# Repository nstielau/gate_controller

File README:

# Gate controller

For alexa enabled gate

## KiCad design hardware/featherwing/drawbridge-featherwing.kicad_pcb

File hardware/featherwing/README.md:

# Drawbridge FeatherWing fabrication package

This is a revision-stamped prototype board for a Feather-compatible host,
including the Unexpected Maker FeatherS3[D] and Adafruit ESP32-S3 Reverse TFT
Feather. It provides the existing, proven 2N3904 transistor output unchanged:
J3 pin 1 is the switched output and J3 pin 2 is the shared ground. The Feather
module is not part of the assembly BOM.

Schematic and PCB signal names use portable Feather header labels:
`WIFI_D5`, `MQTT_D6`, `HOLD_D9`, and `CTRL_D11`. GPIO numbers differ between
Feather models and therefore are not part of these net names.

## PCBWay upload

The generated PCB is `drawbridge-featherwing.kicad_pcb` and the schematic is
`drawbridge-featherwing.kicad_sch`. Generate the fabrication package from the
repository root with:

```sh
make featherwing-fab
```

Every run regenerates the design from `generate.py`, runs ERC/DRC, and replaces
the **entire** `artifacts/featherwing/` directory with a complete release. Do not
keep manual edits or source files in that output directory. Old extracted ZIPs,
previews and reports disappear automatically. Other artifact folders are separate.
If a build fails, the last complete release remains available; its timestamp in
`manifest.json` identifies when it was built. Never upload after a failed build
assuming that the files reflect your latest source changes.

Each build requires a **clean Git checkout**, including staged, unstaged, and
untracked files anywhere in the repository. Commit changes before running the
build. Ignored files such as credentials and `artifacts/` do not block it.
There is no dirty-build override or generation counter.

The revision is exactly the first three characters of Git `HEAD`, for example
`abc`, with no suffix. It appears below the castle and in `manifest.json`.
Every ZIP contains `REV_abc.txt` with both `abc` and the **full commit hash**;
use the full hash to identify a commit unambiguously. Rebuilding the same commit
keeps the same revision. The build checks checkout cleanliness and HEAD again
before replacing the output.

Generation runs on a temporary snapshot of committed sources and leaves the
checkout unchanged. The freshly stamped native KiCad project is exported to
`artifacts/featherwing/design/` and included in the combined ZIP. Open that
project to inspect the current release; tracked native KiCad files are reference
snapshots and may carry an older revision. Incorporate edits into the generator,
commit them, then rebuild.

Prerequisites: KiCad 10 in `/Applications/KiCad`, `make setup`, and the repository's
Node/Playwright installation (`make web-setup`, then `npx playwright install chromium`
if Chromium is missing). Incorporate manual KiCad edits into `generate.py` before
rebuilding because the generator is the design source of record.

PCBWay uploads from `artifacts/featherwing/`:

| Upload field | File |
| --- | --- |
| Gerbers | `drawbridge-featherwing-gerbers.zip` |
| Parts list / BOM | `assembly-bom.xlsx` (PCBWay upload) |
| Centroid | `assembly-position.csv` |
| Assembly other files | `drawbridge-featherwing-assembly-other.zip` |
| Complete package for review | `drawbridge-featherwing-pcbway.zip` |

For Seeed Studio Fusion, upload `seeed-assembly-bom.csv`. It uses Seeed's
four-column `Designator`, `Manufacturer Part Number or Seeed SKU`, `Qty`, and
`Link` format and consolidates identical MPNs. All parts except J3 are selected from Seeed's Shenzhen Open Parts Library
(OPL); their links search the live OPL listing. J3 is Phoenix Contact 1725656
and uses its manufacturer link for external sourcing by Seeed (not verified
OPL stock). The BOM includes the two underside Feather headers, five resistors,
Q1, three LEDs, and J3. The Feather host is excluded. Check live availability when requesting a quote because OPL stock
changes independently of this repository.

The selected XKB headers have 2.54 mm pitch, 2.5 mm insulators, 3.0 mm solder
tails, and 6.0 mm mating pins. Seeed must install their bodies on the bottom of
the wing, with the 6.0 mm pins pointing down into the Feather's sockets. The
LEDs are a matching Everlight 3 mm family; observe the KiCad cathode/pad-1
orientation during assembly.

All three ZIPs are generated together and every member is byte-checked against
the corresponding loose file. Gerbers and drills are also available in `gerbers/`
and `drills/`. Each run refreshes `board.png`, `schematic.pdf`, `schematic.svg`,
`schematic.png`, `silkscreen.svg`, logo SVG/PNG, BOM, positions, `netlist.xml`,
`erc.rpt`, `drc.rpt`, and assembly notes. `manifest.json` records the build time
and SHA-256 for every loose file and ZIP (excluding the manifest itself).
The BOM is emitted as both `assembly-bom.xlsx` for PCBWay and `assembly-bom.csv`
for review. Both include an explicit `Tolerance` column: all five resistors
(R1–R5) have a tolerance of **5%**. R1/R3/R4/R5 are 1 kΩ Yageo
CFR-25JB-52-1K; R2 is 100 kΩ Yageo MFR50SJT-52-100K. Use 5% for the
PCBWay assembly specification; 1% is not required.

The isometric castle logo uses a 14 × 14 mm SVG canvas with 0.18 mm strokes.
The actual mark occupies about 12 × 12.5 mm on the USB end. The generator imports
`assets/drawbridge-silkscreen.svg` directly into F.Silkscreen. The 840-pixel PNG
is generated from that same SVG as a reference; no separate logo placement by
PCBWay is needed. For a bare-board order, only the Gerbers and drill files are
needed. For assembly, select through-hole assembly and ask PCBWay to
confirm the listed manufacturer part numbers and header availability. J3 is a
top-side screw terminal at the right-hand edge, with wire entry facing outward
away from the USB connector.

Recommended starting options are two layers, FR-4, 1.6 mm thickness, 1 oz
copper, green solder mask, white silkscreen, and lead-free HASL. These are
defaults for quoting, not a manufacturing release.

## Release checks

Run `make featherwing-check` before uploading; it performs the same complete
rebuild as `make featherwing-fab`. Offline package freshness/failure recovery
tests run with `.venv/bin/python -m unittest test_suite.test_featherwing_fab`
and are included in `make test`. Inspect
the Gerbers in PCBWay's viewer, especially the Feather header orientation,
mounting holes, J3 polarity, and the antenna keepout at the FeatherS3[D] end.

The gate-controller interface remains installation-specific. The transistor
stage is retained because it is the known-working circuit. J3 is populated with
[Phoenix Contact MPT 0,5/2-2,54, 1725656](https://www.phoenixcontact.com/us/products/1725656).
Viewed from above with USB left, the upper screw is GND (pin 2) and the lower
screw is OUT_OC (pin 1). Follow these labels when reconnecting existing wires.
The terminal has a 5.54 x 6.2 mm body, 8.5 mm installed height, and 2.54 mm
contact pitch. Use 20–26 AWG wire, strip 4.5 mm, and tighten to 0.12–0.15 N m
while supporting the terminal body. Provide cable strain relief.

The local `Drawbridge:ExitTerminal` footprint retains KiCad's Phoenix footprint
contacts and both 1.1 mm non-plated locating holes from the manufacturer's
drilling drawing, 2.54 mm toward the wire-entry side of the contact pins. It
uses a 0.25 mm body courtyard and omits silkscreen at the wire-entry edge. Do not omit
these holes or substitute a generic 2.54 mm header footprint. J3 is included in
all assembly BOMs and in the top-side position file. The headers remain on the
underside. The board outline is unchanged at 50.8 x 22.86 mm.

Routing uses horizontal, vertical, and 45-degree segments, with chamfers at
right-angle turns. Connected branches may still meet at right angles; these
are electrical junctions, not sharp bends in a continuous route. Copper/holes,
component courtyards, and silkscreen are checked on every fabrication build.
The terminal and cable are near the Feather's antenna end: RF performance and
assembled stack/enclosure clearance need checking with the actual host. DRC
does not establish either of those physical properties.

The Feather-compatible J1 (16-pin) and J2 (12-pin) stacking headers are
bottom-side assembly parts. Their XY pin coordinates are intentionally not
mirrored, preserving the Feather pin order when this board is placed on top of
the Feather host.

## Indicator LEDs

The 3 mm through-hole LEDs in the assembly BOM are assigned as follows:

| Reference | Function | Color |
| --- | --- | --- |
| D1 | Wi-Fi | Cool white |
| D2 | MQTT | Blue |
| D3 | Hold | Green |

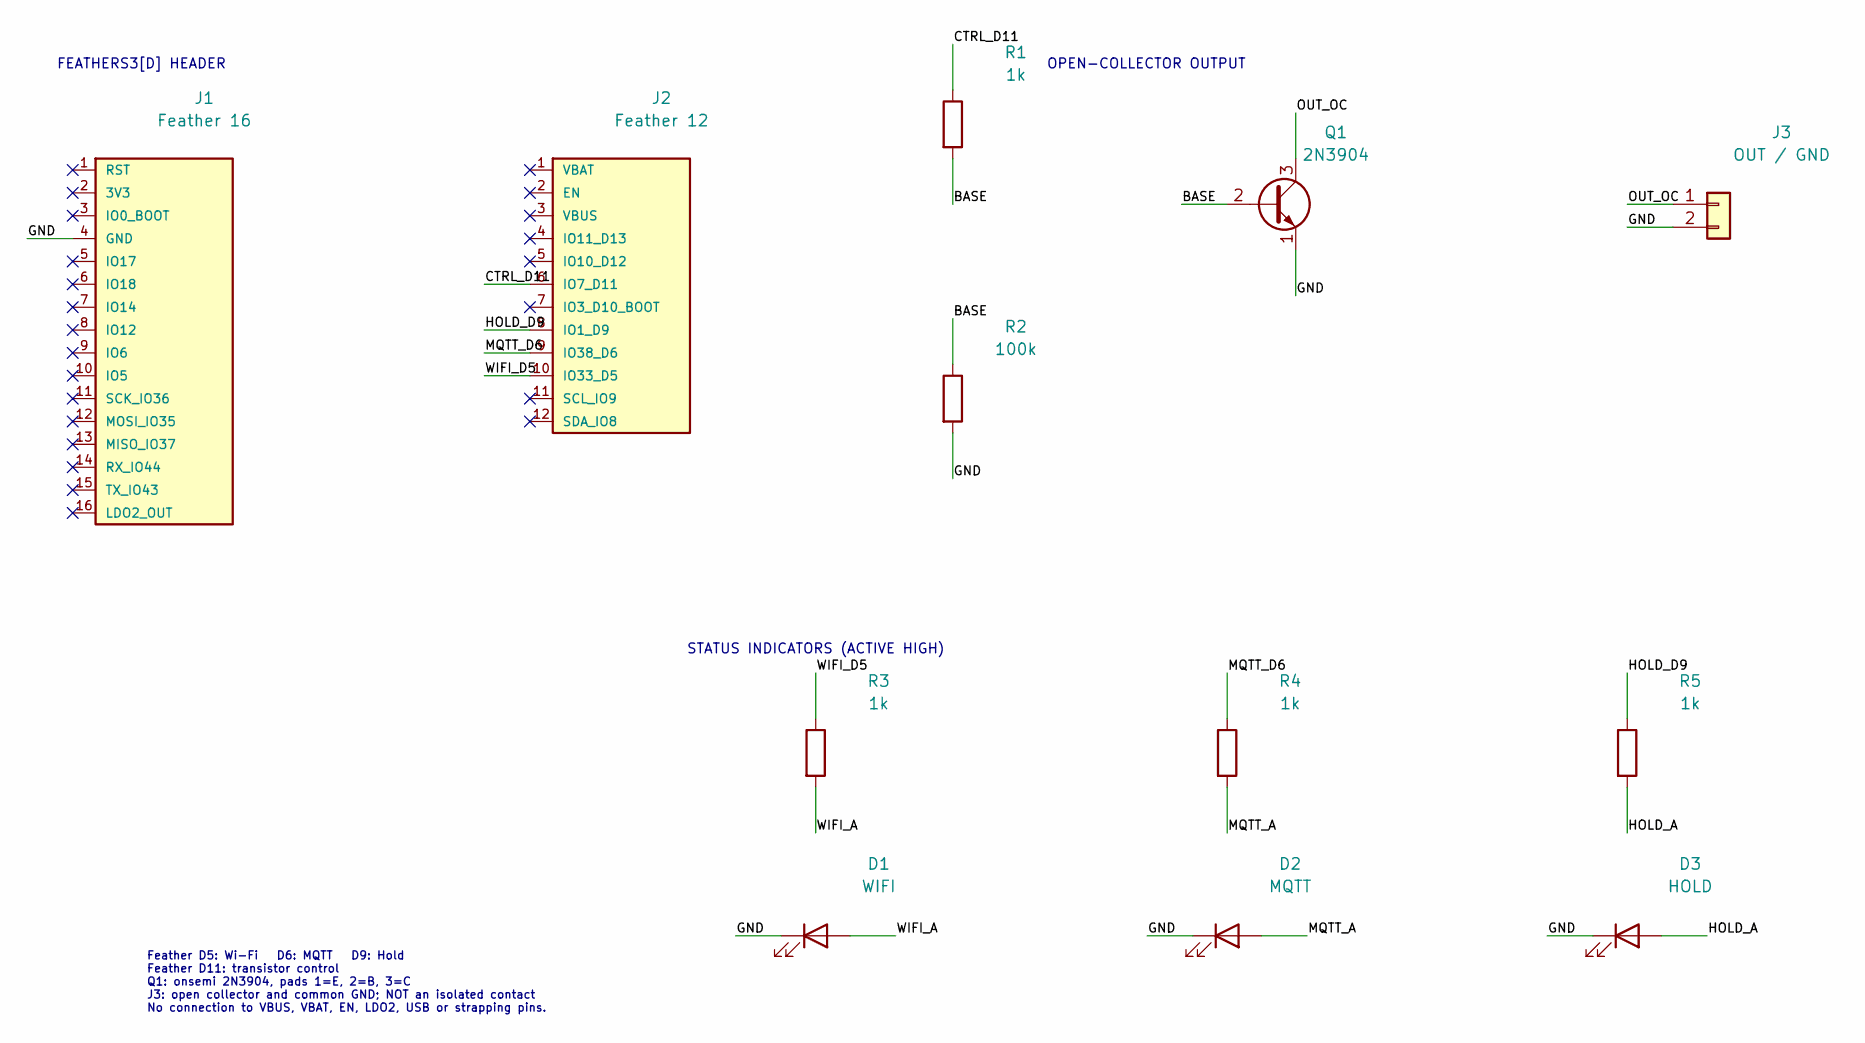
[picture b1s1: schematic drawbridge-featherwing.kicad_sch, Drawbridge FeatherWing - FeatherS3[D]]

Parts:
D1: WIFI; LED_D3.0mm
D2: MQTT; LED_D3.0mm
D3: HOLD; LED_D3.0mm
J1: Feather 16; FeatherHeader16
J2: Feather 12; FeatherHeader12
J3: OUT / GND; ExitTerminal
Q1: 2N3904; TO-92_Inline
R1, R3, R4, R5: 1k; R_Axial_DIN0207_L6.3mm_D2.5mm_P7.62mm_Horizontal
R2: 100k; R_Axial_DIN0207_L6.3mm_D2.5mm_P7.62mm_Horizontal

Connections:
/BASE: Q1.2 (B), R1.2, R2.1
/CTRL_D11: J2.6 (IO7_D11), R1.1
/GND: D1.1 (K), D2.1 (K), D3.1 (K), J1.4 (GND), J3.2, Q1.1 (E), R2.2
/HOLD_A: D3.2 (A), R5.2
/HOLD_D9: J2.8 (IO1_D9), R5.1
/MQTT_A: D2.2 (A), R4.2
/MQTT_D6: J2.9 (IO38_D6), R4.1
/OUT_OC: J3.1, Q1.3 (C)
/WIFI_A: D1.2 (A), R3.2
/WIFI_D5: J2.10 (IO33_D5), R3.1

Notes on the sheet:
FEATHERS3[D] HEADER
OPEN-COLLECTOR OUTPUT
STATUS INDICATORS (ACTIVE HIGH)
Feather D5: Wi-Fi D6: MQTT D9: Hold Feather D11: transistor control Q1: onsemi 2N3904, pads 1=E, 2=B, 3=C J3: open collector and common GND; NOT an isolated contact No connection to VBUS, VBAT, EN, LDO2, USB or strapping pins.

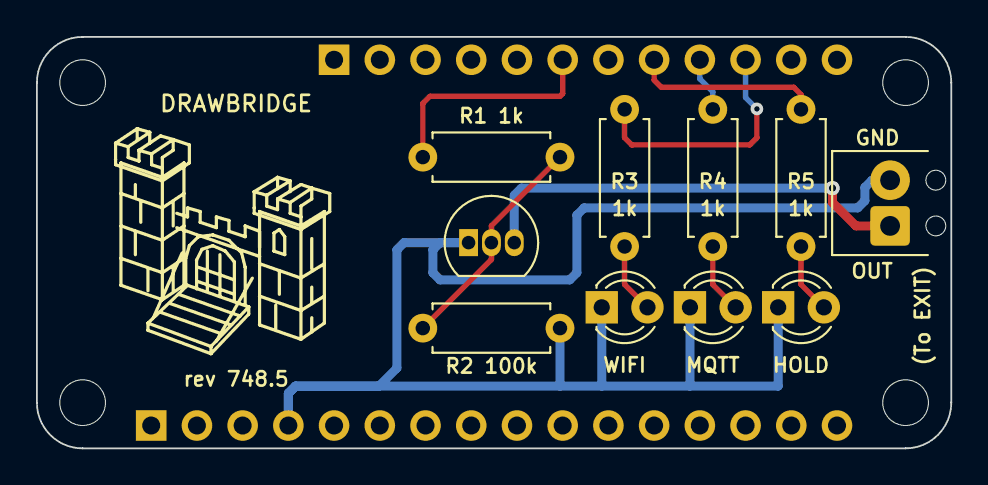
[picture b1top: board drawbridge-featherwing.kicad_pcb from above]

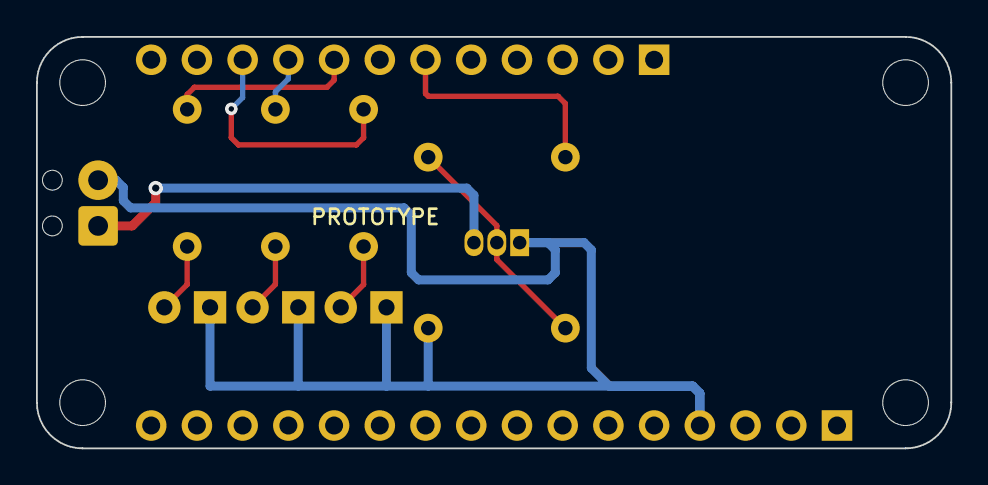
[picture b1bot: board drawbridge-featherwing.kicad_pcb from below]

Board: 2 copper layers, 50.8 x 22.9 mm, 16 parts (2 on the bottom side), 10 nets.

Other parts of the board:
H1, H2, H3, H4: MountingHole_2.5mm; FeatherMount

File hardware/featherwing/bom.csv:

Reference,Value,Description,Manufacturer,Manufacturer Part Number,Footprint,Quantity,Populate
J1,Feather 16,"Feather-compatible 1x16 male header, 2.54 mm, 3/6 mm pins",XKB,X6511WV-16H-C30D60,Drawbridge:FeatherHeader16,1,Yes
J2,Feather 12,"Feather-compatible 1x12 male header, 2.54 mm, 3/6 mm pins",XKB,X6511WV-12H-C30D60,Drawbridge:FeatherHeader12,1,Yes
R1,1k,"1 kOhm 5% axial resistor, 0.25 W",Yageo,CFR-25JB-52-1K,Resistor_THT:R_Axial_DIN0207_L6.3mm_D2.5mm_P7.62mm_Horizontal,1,Yes
R2,100k,"100 kOhm 5% axial resistor, 0.5 W",Yageo,MFR50SJT-52-100K,Resistor_THT:R_Axial_DIN0207_L6.3mm_D2.5mm_P7.62mm_Horizontal,1,Yes
Q1,2N3904,"NPN transistor, TO-92, EBC",onsemi,2N3904BU,Package_TO_SOT_THT:TO-92_Inline,1,Yes
J3,OUT / GND,"2-position screw terminal, 2.54 mm, side wire entry",Phoenix Contact,1725656,Drawbridge:ExitTerminal,1,Yes
R3,1k,"1 kOhm 5% axial resistor, 0.25 W",Yageo,CFR-25JB-52-1K,Resistor_THT:R_Axial_DIN0207_L6.3mm_D2.5mm_P7.62mm_Horizontal,1,Yes
D1,WIFI,"3 mm cool-white LED, THT",Everlight,204-15UTC/S400-X9,LED_THT:LED_D3.0mm,1,Yes
R4,1k,"1 kOhm 5% axial resistor, 0.25 W",Yageo,CFR-25JB-52-1K,Resistor_THT:R_Axial_DIN0207_L6.3mm_D2.5mm_P7.62mm_Horizontal,1,Yes
D2,MQTT,"3 mm blue LED, THT",Everlight,204-10SUBC/S400-A4,LED_THT:LED_D3.0mm,1,Yes
R5,1k,"1 kOhm 5% axial resistor, 0.25 W",Yageo,CFR-25JB-52-1K,Resistor_THT:R_Axial_DIN0207_L6.3mm_D2.5mm_P7.62mm_Horizontal,1,Yes
D3,HOLD,"3 mm green LED, THT",Everlight,204-10SUGD/S400-A5,LED_THT:LED_D3.0mm,1,Yes

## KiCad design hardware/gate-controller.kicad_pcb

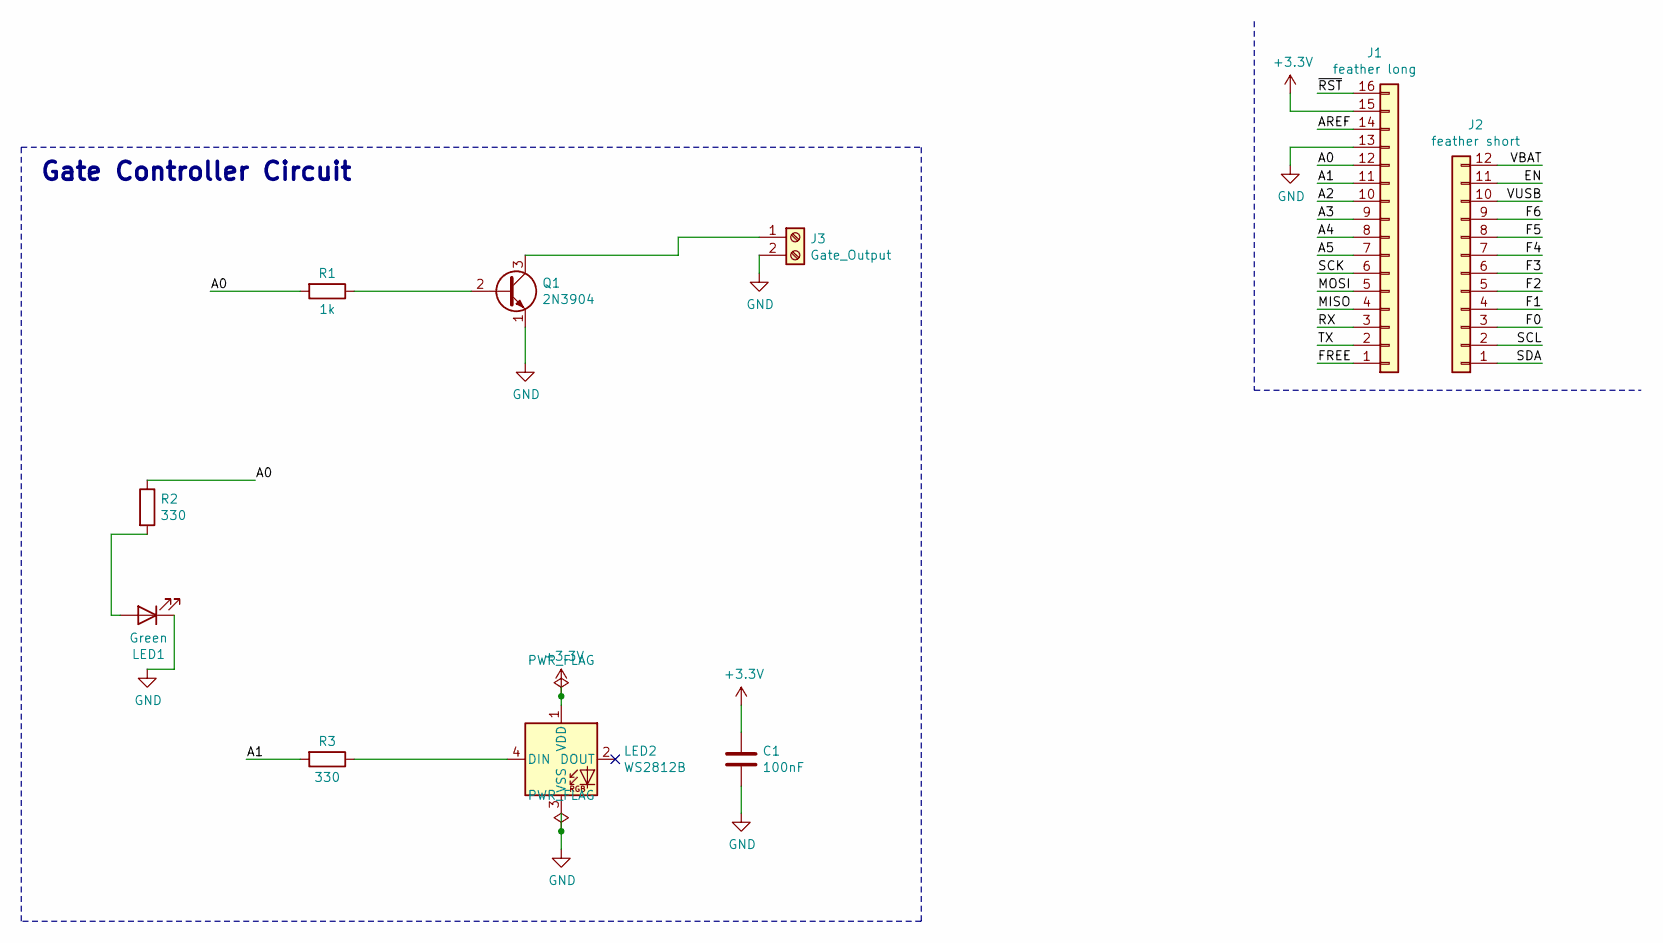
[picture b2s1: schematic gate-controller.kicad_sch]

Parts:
C1: 100nF; C_0805_2012Metric
J1: feather long; PinHeader_1x16_P2.54mm_Vertical
J2: feather short; PinHeader_1x12_P2.54mm_Vertical
J3: Gate_Output; TerminalBlock_Phoenix_MKDS-1,5-2-5.08_1x02_P5.08mm_Horizont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
LED1: Green; LED_0805_2012Metric
LED2: WS2812B; LED_WS2812B_PLCC4_5.0x5.0mm_P3.2mm
Q1: 2N3904; TO-92_Inline
R1: 1k; R_0805_2012Metric
R2, R3: 330; R_0805_2012Metric

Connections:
+3.3V: C1.1, J1.15, LED2.1 (VDD)
/A0: J1.12, R1.2, R2.1
/A1: J1.11, R3.2
/A2: J1.10
/A3: J1.9
/A4: J1.8
/A5: J1.7
/AREF: J1.14
/EN: J2.11
/F0: J2.3
/F1: J2.4
/F2: J2.5
/F3: J2.6
/F4: J2.7
/F5: J2.8
/F6: J2.9
/FREE: J1.1
/MISO: J1.4
/MOSI: J1.5
/RX: J1.3
/SCK: J1.6
/SCL: J2.2
/SDA: J2.1
/TX: J1.2
/VBAT: J2.12
/VUSB: J2.10
/~RST: J1.16
GND: C1.2, J1.13, J3.2, LED1.1 (K), LED2.3 (VSS), Q1.1 (E)
unnamed: J3.1, Q1.3 (C)
unnamed: LED1.2 (A), R2.2
unnamed: LED2.4 (DIN), R3.1
unnamed: Q1.2 (B), R1.1

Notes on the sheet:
Gate Controller Circuit

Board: 2 copper layers, 10 parts (2 on the bottom side), 8 nets, no tracks yet.

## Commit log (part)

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2022-09-05 First pass
2022-09-05 Setting base image.
2022-09-05 Ordering callback definition
2022-09-05 A deep and dreamless slumber
2022-09-05 Prime output
2022-09-06 Lighting while held.
2022-09-06 Pull up
2022-09-14 Test skeleton
2022-09-14 Pip packages
2022-09-14 Adding server functionality
2022-09-14 Adding basic gate controller
2022-09-14 Initial readme.
2023-03-12 Exposing is_conneted.
2023-03-12 Fix, importing response.
2023-03-12 Fix, using private var naming.
2023-03-12 Properly initializing.
2023-03-27 Using more accurate constant name for pin.
2023-03-27 Changing semantics to more closely match the use-case.
2023-03-27 Syntax fix.
2023-03-28 Using unique method names for routes.
2023-03-28 Avoiding using DELETE
2026-06-18 Add KiCad FeatherWing PCB template for gate controller board
2026-06-18 Add FeatherWing gate controller PCB design spec
2026-06-18 Add FeatherWing PCB implementation plan
2026-06-18 Add .gitignore for KiCad temp files
2026-06-18 Update README with hardware docs and BOM
